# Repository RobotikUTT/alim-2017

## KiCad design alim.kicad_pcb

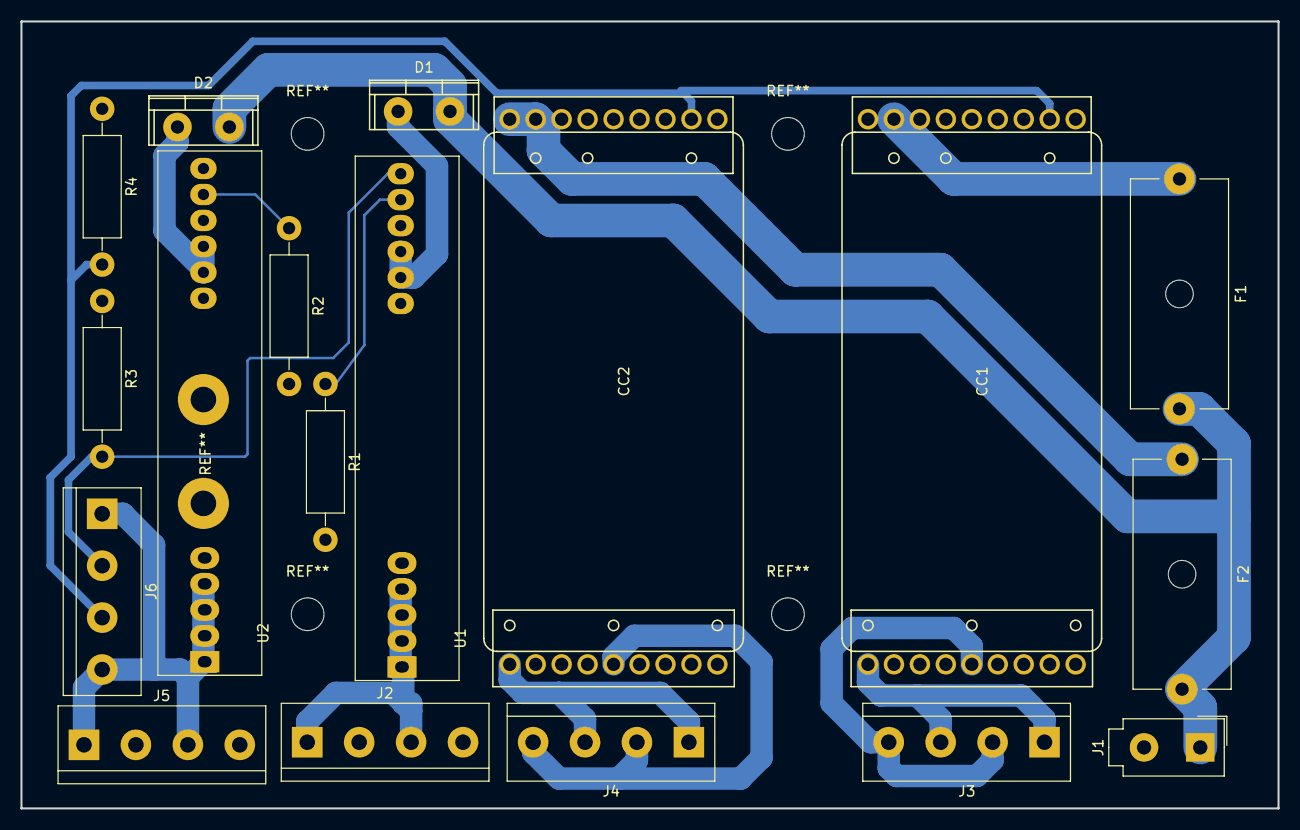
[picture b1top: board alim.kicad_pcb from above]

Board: 2 copper layers, 123.0 x 77.0 mm, 18 parts (0 on the bottom side), 16 nets.

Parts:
CC1, CC2: TEN50; Traco_TEN50_Molex
D1, D2: IDH06SG60C; TO-220-2
F1, F2: 10A; Fuseholder5x20_horiz_open_Schurter_0031_8201
J1: BATT; Molex_MiniFit-JR-5556-02A_2x01x4.20mm_Straight
J2: Out5P; bornier4
J3: Out12L; bornier4
J4: Out12R; bornier4
J5: Out5L; bornier4
J6: AU; bornier4
R1, R2: 1.472k; R_Axial_DIN0411_L9.9mm_D3.6mm_P15.24mm_Horizontal
R3, R4: 10k; R_Axial_DIN0411_L9.9mm_D3.6mm_P15.24mm_Horizontal
U1, U2: OKX-T/10-D12; Murata_OKX-T10-D12N-C

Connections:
+5V: J5.1, J5.3, J6.1, J6.4, U2.1, U2.2, U2.3, U2.4
+BATT: D1.2, D2.2, F1.2, F2.2, J1.1
/En_P5: J6.2, R3.2, U1.11
GND: CC1.2, CC2.2, J1.2, J2.2, J2.4, J5.2, J5.4, R1.2, R2.2, R3.1, R4.1, U1.5, U1.6, U2.5, U2.6, U2.11
unnamed: CC1.1, F1.1
unnamed: CC1.3, CC2.3, J6.3, R4.2
unnamed: CC1.4, J3.1, J3.3
unnamed: CC1.5, J3.2, J3.4
unnamed: CC2.1, F2.1
unnamed: CC2.4, J4.1, J4.3
unnamed: CC2.5, J4.2, J4.4
unnamed: D1.1, U1.7, U1.8
unnamed: D2.1, U2.7, U2.8
unnamed: J2.1, J2.3, U1.1, U1.2, U1.3, U1.4
unnamed: R1.1, U1.10
unnamed: R2.1, U2.10

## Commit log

2017-05-23 Carte alim C2017
2017-05-24 Add gitignore
2017-05-24 Add out files
2017-05-24 Add datasheets
